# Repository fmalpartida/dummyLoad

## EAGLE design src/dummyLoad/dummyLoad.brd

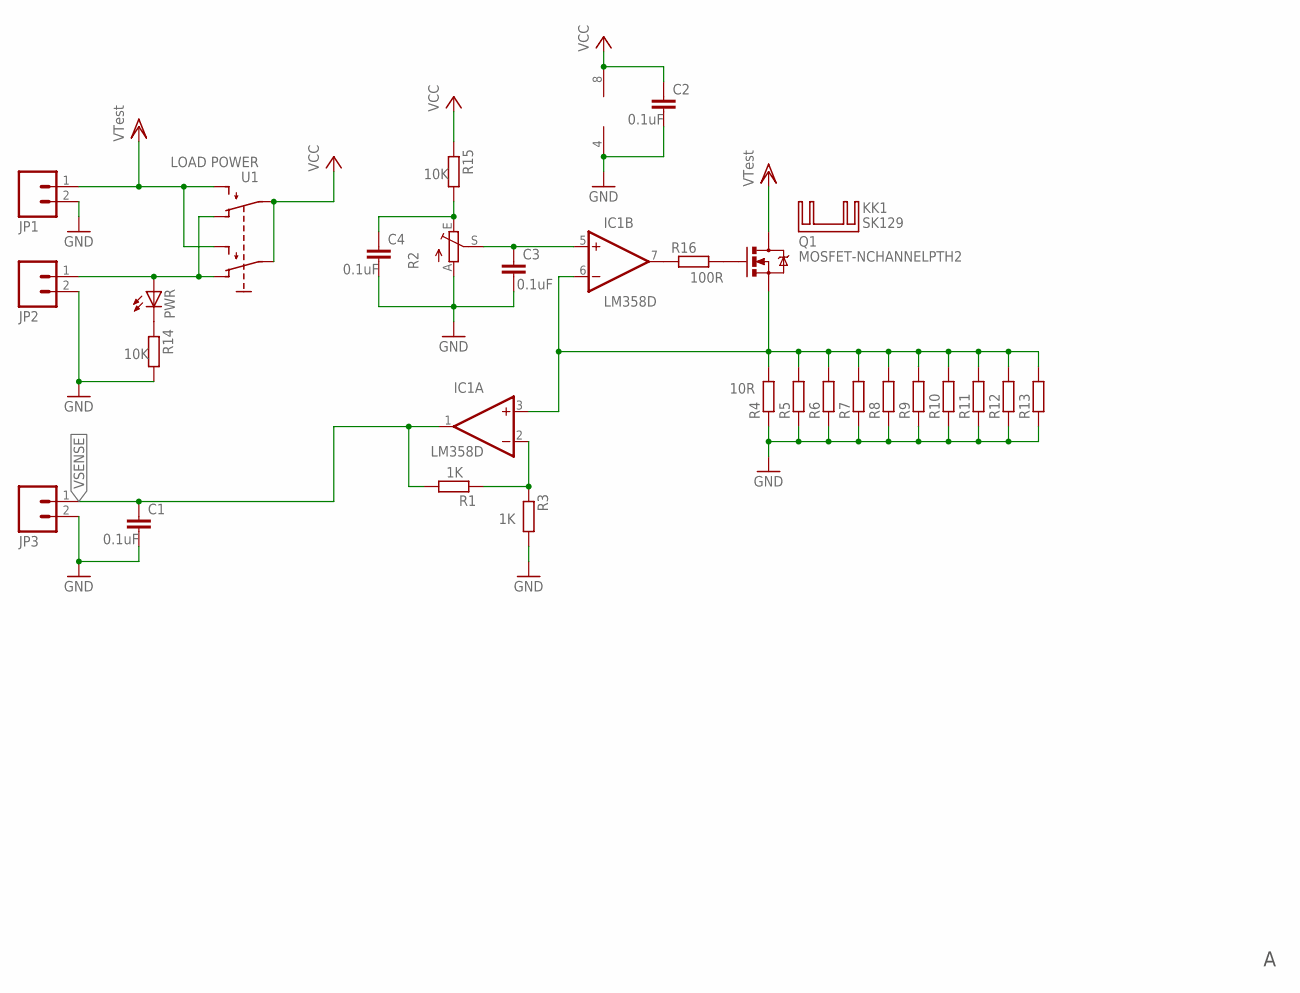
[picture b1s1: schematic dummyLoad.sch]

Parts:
C1, C2, C3, C4: 0.1uF; C0805
IC1: LM358D; SO08
JP1, JP2, JP3: M02PTH; 1X02
KK1: SK129; SK129-HOLE
PWR: LEDCHIPLED_0805; CHIPLED_0805
Q1: MOSFET-NCHANNELPTH2; TO220V
R1, R3: 1K; M0805
R2: TRIM_EU-B64Y; B64Y
R4: 10R; M0805
R5, R6, R7, R8, R9, R10, R11, R12, R13: R-EU_M0805; M0805
R14, R15: 10K; M0805
R16: 100R; M0805
U1: LOAD POWER; SWITCH-JS202011

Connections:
GND: C1.2, C2.2, C3.2, C4.2, IC1.4 (V-), JP1.2, JP2.2, JP3.2, R2.A, R3.2, R4.1, R5.1, R6.1, R7.1, R8.1, R9.1, R10.1, R11.1, R12.1, R13.1, R14.2
unnamed: JP2.1, PWR.A, U1.P1 (O), U1.P4 (O1)
unnamed: IC1.2 (-IN), R1.1, R3.1
unnamed: C4.1, R2.E, R15.2
unnamed: IC1.7 (OUT), R16.1
unnamed: C3.1, IC1.5 (+IN), R2.S
unnamed: PWR.C, R14.1
unnamed: Q1.1 (G), R16.2
unnamed: IC1.3 (+IN), IC1.6 (-IN), Q1.3 (S), R4.2, R5.2, R6.2, R7.2, R8.2, R9.2, R10.2, R11.2, R12.2, R13.2
VCC: C2.1, IC1.8 (V+), R15.1, U1.P2, U1.P5 (P1)
VDD: JP1.1, Q1.2 (D), U1.P3 (S), U1.P6 (S1)
VSENSE: C1.1, IC1.1 (OUT), JP3.1, R1.2

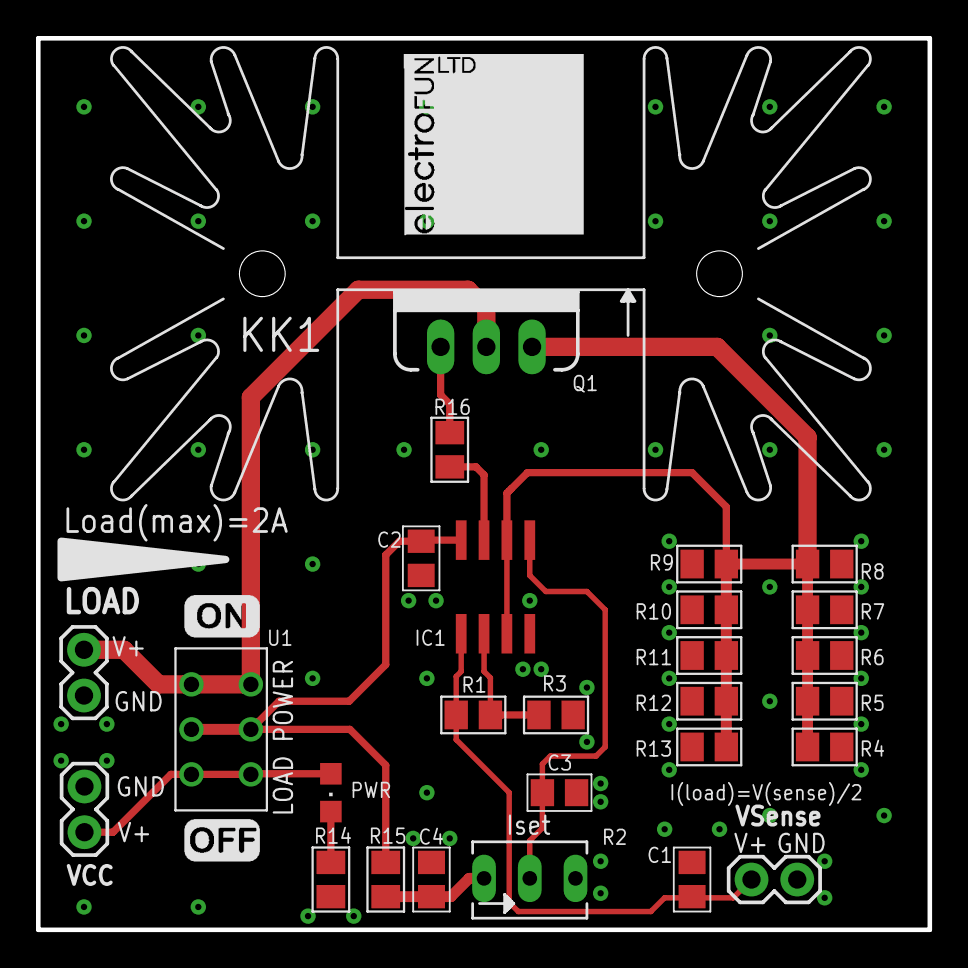
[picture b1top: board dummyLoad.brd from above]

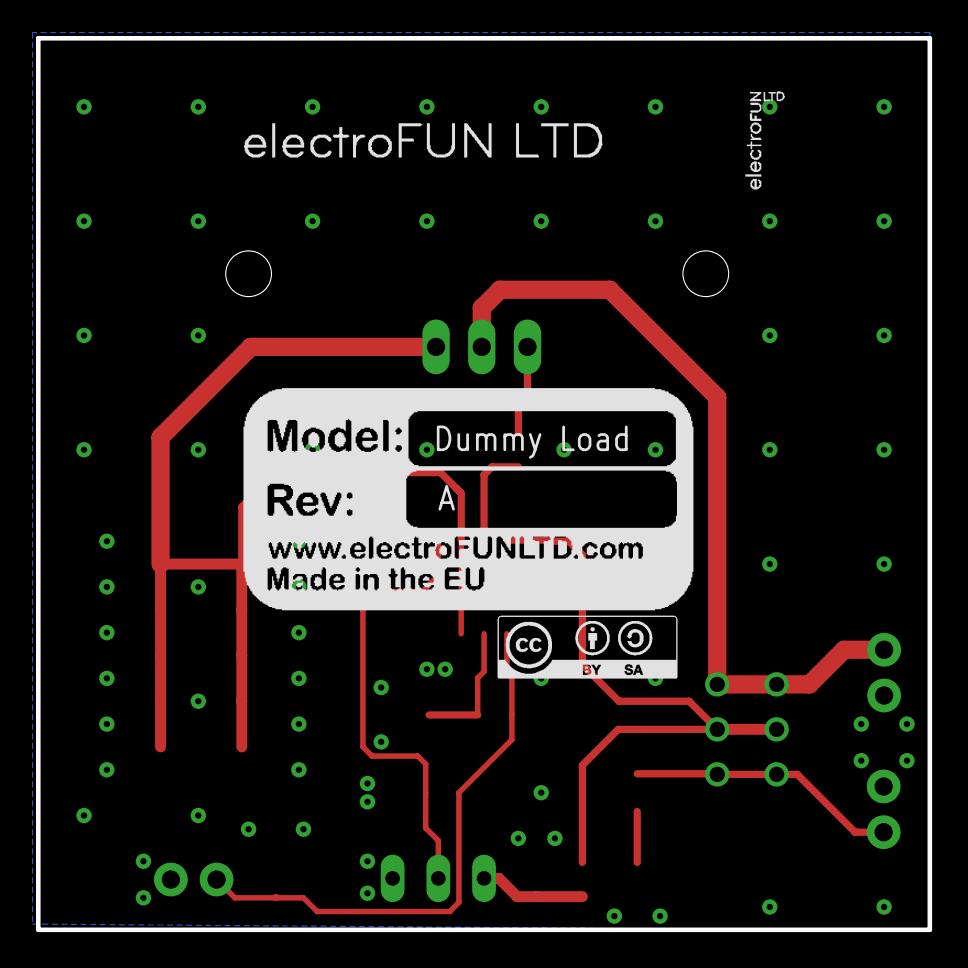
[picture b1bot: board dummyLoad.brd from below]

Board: 2 copper layers, 49.5 x 49.5 mm, 34 parts (3 on the bottom side), 12 nets.

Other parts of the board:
U$1: ELECTROFUN_10X10
U$2: ON
U$3: ELECTROFUN_STRIP
U$4: SA-BY
U$5: OFF
U$6: BOARD_REF

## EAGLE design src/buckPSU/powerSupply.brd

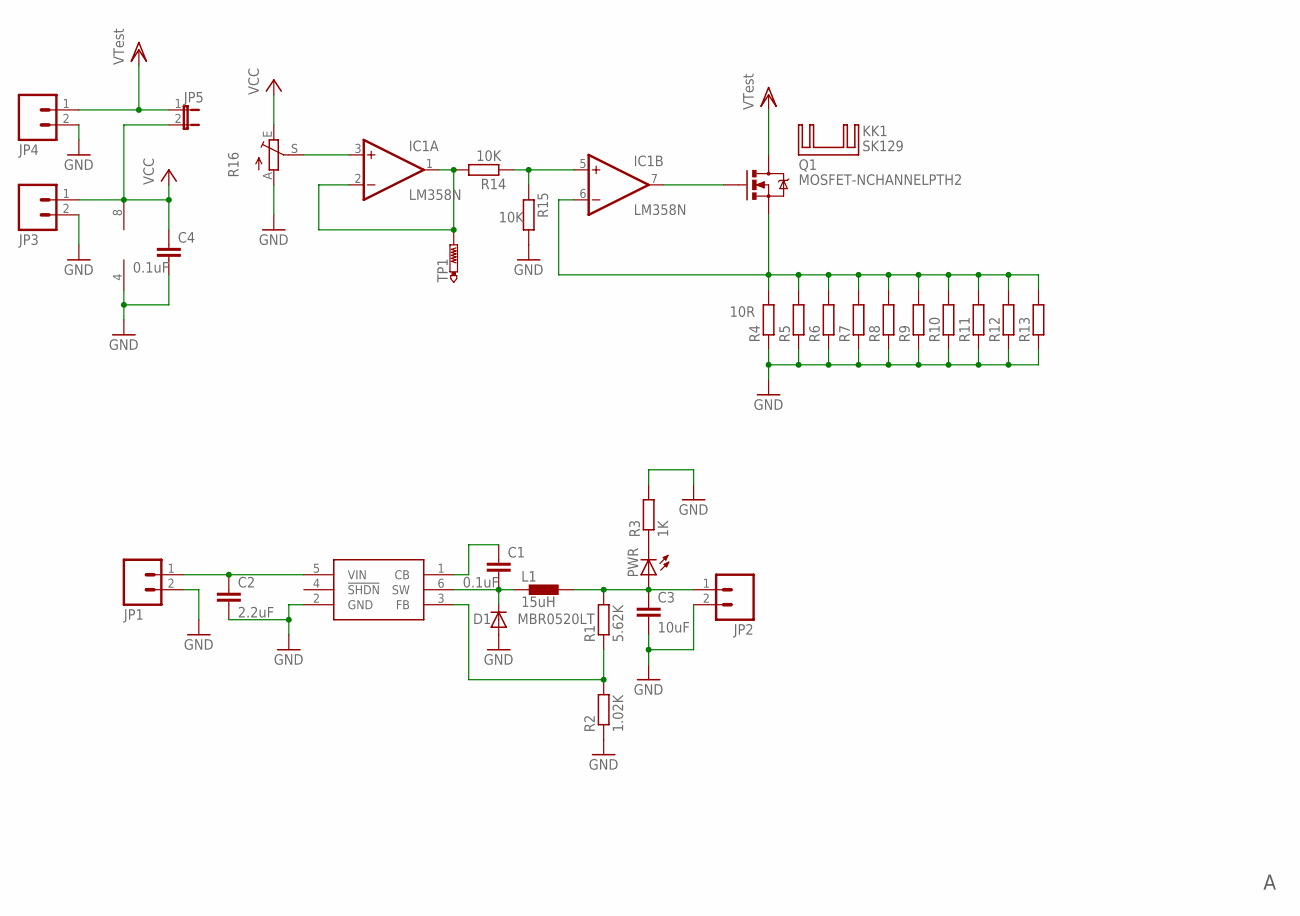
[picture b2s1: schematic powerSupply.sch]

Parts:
C1, C4: 0.1uF; C0805
C2: 2.2uF; C1206
C3: 10uF; C1206
D1: MBR0520LT; SOD123
IC1: LM358N; DIL08
JP1, JP2, JP3, JP4: M02PTH; 1X02
JP5: JUMPER-2PTH; 1X02
KK1: SK129; SK129-HOLE
L1: 15uH; LQH
PWR: LEDCHIPLED_0805; CHIPLED_0805
Q1: MOSFET-NCHANNELPTH2; TO220V
R1: 5.62K; M0805
R2: 1.02K; M0805
R3: 1K; M0805
R4: 10R; M0805
R5, R6, R7, R8, R9, R10, R11, R12, R13: R-EU_M0805; M0805
R14, R15: 10K; M0805
R16: TRIM_EU-B64Y; B64Y
TP1: PTR1TP20R; TP20R
U1: LM2841; TSOT6

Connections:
GND: C2.2, C3.2, C4.2, D1.A, IC1.4 (V-), JP1.2, JP2.2, JP3.2, JP4.2, R2.1, R3.2, R4.1, R5.1, R6.1, R7.1, R8.1, R9.1, R10.1, R11.1, R12.1, R13.1, R15.2, R16.A, U1.2 (GND)
unnamed: C1.2, D1.C, L1.1, U1.6 (SW)
unnamed: C1.1, U1.1 (CB)
unnamed: C3.1, JP2.1, L1.2, PWR.A, R1.2
unnamed: R1.1, R2.2, U1.3 (FB)
unnamed: PWR.C, R3.1
unnamed: C2.1, JP1.1, U1.5 (VIN)
unnamed: IC1.7 (OUT), Q1.1 (G)
unnamed: IC1.5 (+IN), R14.1, R15.1
unnamed: IC1.1 (OUT), IC1.2 (-IN), R14.2, TP1.TP
unnamed: IC1.3 (+IN), R16.S
unnamed: IC1.6 (-IN), Q1.3 (S), R4.2, R5.2, R6.2, R7.2, R8.2, R9.2, R10.2, R11.2, R12.2, R13.2
VCC: C4.1, IC1.8 (V+), JP3.1, JP5.2, R16.E
VDD: JP4.1, JP5.1, Q1.2 (D)

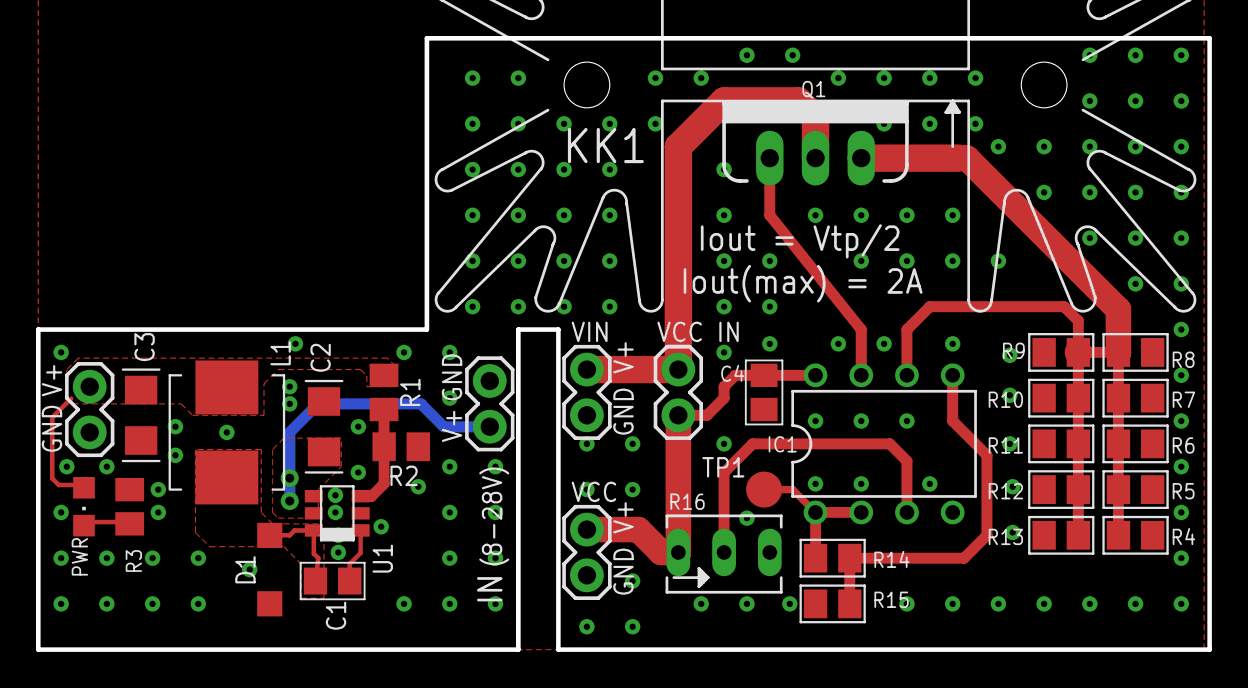
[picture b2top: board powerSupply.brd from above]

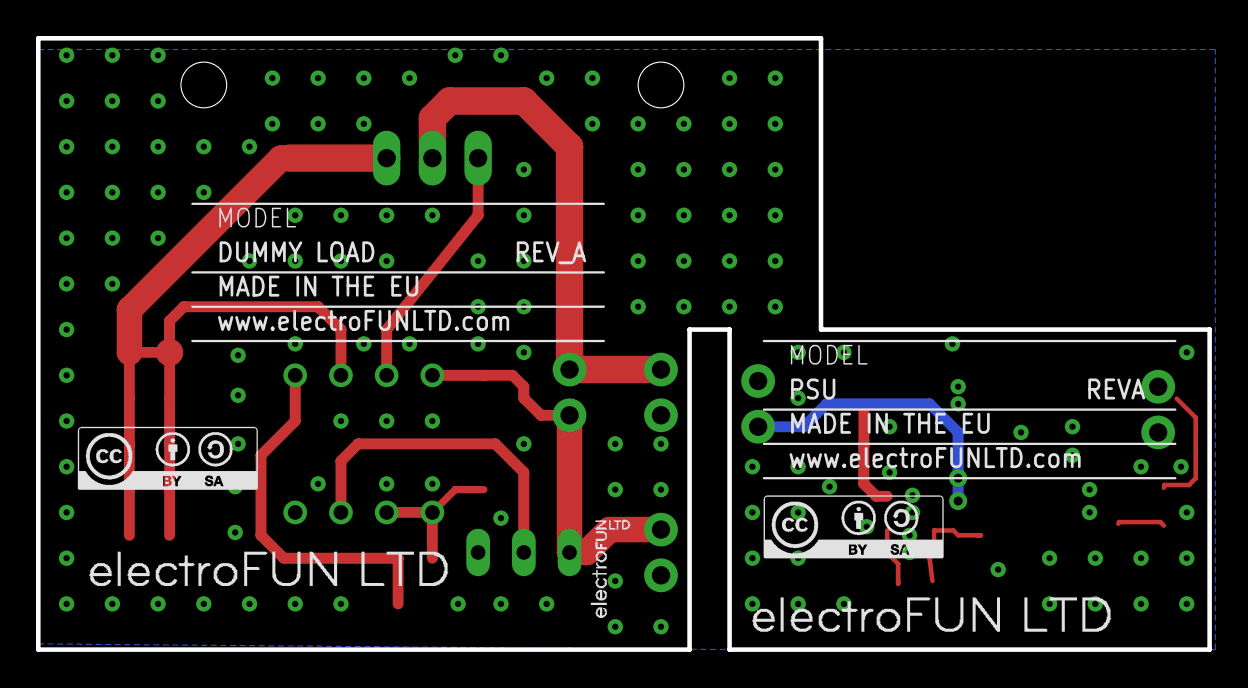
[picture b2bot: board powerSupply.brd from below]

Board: 2 copper layers, 65.1 x 34.0 mm, 39 parts (6 on the bottom side), 14 nets.

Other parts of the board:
REVA: PSU; BOARD_INFO_LARGE
REV_A: DUMMY LOAD; BOARD_INFO_LARGE
U$1, U$3: ELECTROFUN_STRIP
U$2, U$4: SA-BY

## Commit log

2016-05-21 Dummy load first version.
2016-06-25 Minor updates to PCB and layout

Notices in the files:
parts and their libraries:
SparkFun: Licensing: CC v3.0 Share-Alike You are welcome to use this library for commercial purposes.
